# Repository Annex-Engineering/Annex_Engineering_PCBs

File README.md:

# PCBs

PCBs Designed by Annex Engineering Members

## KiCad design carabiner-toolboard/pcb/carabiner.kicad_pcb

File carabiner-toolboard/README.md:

# Carabiner-Toolboard

The carabiner is a toolboard for easy & quick connection between the backpack and toolhead.

It was inspired by the first iterations of dumbboard by LukesLab and designed to bring the idea of a 'simple toolboard' to the next level!

## Features

- Input via 16pin horizontal/vertical microfit
- Two outputs for partcooling fans
- Soldered seperate voltage selection for hotend fan and partcooling fan
   - Uses either the hotend voltage or one alternative voltage
- Thermistor for the chamber
  - Supports any size from 0603 to 1206
- BAT85 diode for inductive probes

## Connectors & Amperage

_Note: All amperage-values have been designed to work in an enclosed printer with up to 65° chamber temperature & have  some safety margins. While you could use higher ampere in an open-frame printer, it's highly discouraged. <br/>
When multiple connectors are supported **bold** marks the recommended connector._

|   | Supported Connectors | Maximum Ampere |
| ------------- | ------------- | ------------- | 
| Hotend  | 2-pin JST XH <br/> Microfit 430450227 <br/> **Microfit 436500227** (compatible with e3d heater) | ~2 Ampere (50W heater on 24V) <br/> 4.2 Ampere (100W heater on 24V) <br/>4.2 Ampere (100W heater on 24V)
| Hotend Thermistor  | 2-pin JST XH <br/> **Microfit 436500227** (compatible with e3d thermistor) | / <br/> /
| Hotend Fan | 2-pin JST XH | 1 Ampere
| 2x Partcooling Fan | 2-pin JST XH | 2 Ampere (total for both)
| Stepper | 4-pin JST XH | 1.2 Ampere <br/> 0.84 Ampere on TMC drivers as you specify the RMS ampere which is ~70% of peak
| Aux / Probe | 4-pin JST XH | 0.8 Ampere

## BOM / Parts

Find the latest BOM in the [Annex Sourcing Guide](https://docs.google.com/spreadsheets/d/1O3eyVuQ6M4F03MJSDs4Z71_XyNjXL5HFTZr1jsaAtRc) under PCBs

## Build Guide

[Please check out this simple written build guide](buildguide/README.md).

## Wiring Guide

This pinout assumes you're looking directly at the cable. 

| PinNumber | Usage  | Silk on PCB | PinNumber | Usage | Silk on PCB | 
|-------------|:-------------:|:-------------:| ------------- |:-------------:|:-------------:|
| 1  |  Thermistor Chamber | ThChamb | 9 | Hotend Voltage | Main+
| 2  | Partcooling Fans Ground | PCF- | 10 | Hotend Ground | HE-
| 3  | Hotend Fan Ground | HEF- | 11 | Alt Voltage | Alt+
| 4  | Thermistor Common Ground | ThGnd | 12 | Thermistor Hotend | ThHE
| 5  | Motor A | 1A | 13 | Motor C | 2A
| 6  | Motor B | 1B | 14 | Motor D | 2B
| 7  | Aux 1 | A1 | 15 | Aux 2 | A2
| 8  | Aux 4 | A4 | 16 | Aux 3 | A3

## Gallery

Side A and B of the R1.1 PCB

## Discord
Our discord server can be found here:

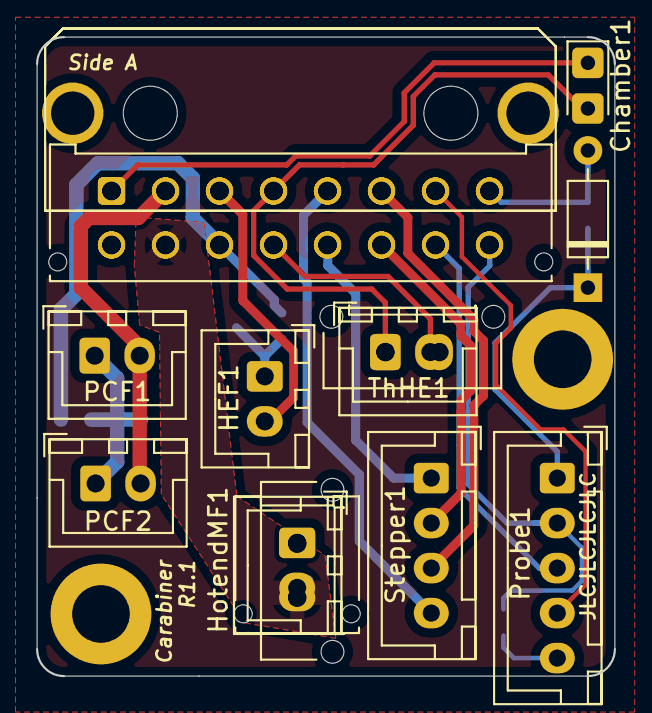
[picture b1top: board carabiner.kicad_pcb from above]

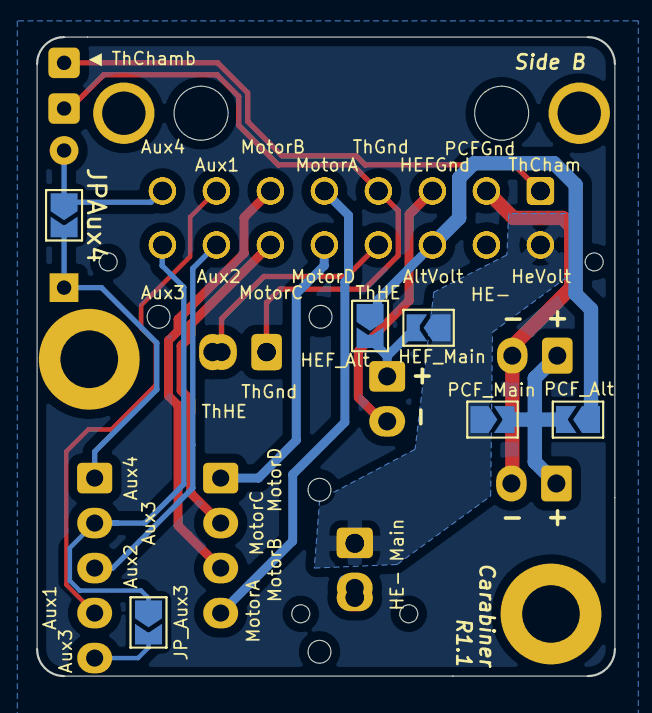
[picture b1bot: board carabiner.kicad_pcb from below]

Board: 2 copper layers, 32.1 x 35.5 mm, 25 parts (6 on the bottom side), 20 nets.

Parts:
Chamber1: Thermistor; 0603_to_1206_THT
D1: B350; D_DO-35_SOD27_P7.62mm_Horizontal
H1, H2: MountingHole; MountingHole_3.2mm_M3_DIN965_Pad
HEF1: HotendFan; JST_XH_B2B-XH-A_1x02_P2.50mm_Vertical
HEF_Alt: SolderJumper_2_Open; SolderJumper-2_P1.3mm_Open_TrianglePad1.0x1.5mm
HEF_Main: SolderJumper_2_Open; SolderJumper-2_P1.3mm_Open_TrianglePad1.0x1.5mm
HotendMF1: Hotend MF 43650-0215; Molex_Micro-Fit_3.0_43650-0215_1x02_P3.00mm_Vertical
HotendMF2: Hotend MF 43045-0212; Molex_Micro-Fit_3.0_43045-0212_2x01_P3.00mm_Vertical
HotendXH1: HotendXHTool; JST_XH_B2B-XH-A_1x02_P2.50mm_Vertical
J1: MF-Vertical 43045-1612; Molex_Micro-Fit_3.0_43045-1612_2x08_P3.00mm_Vertical
J2: MF-Horizontal 43045-1621; Molex_Micro-Fit_3.0_43045-1621_2x08-1MP_P3.00mm_Horizontal
J7: MF-Horizontal 43045-1600; Molex_Micro-Fit_3.0_43045-1600_2x08_P3.00mm_Horizontal
JPAux4: SolderJumper_2_Open; SolderJumper-2_P1.3mm_Open_TrianglePad1.0x1.5mm
JP_Aux3: SolderJumper_2_Open; SolderJumper-2_P1.3mm_Open_TrianglePad1.0x1.5mm
LOGO1: Logo_Open_Hardware_Small; AnnexLogo
LOGO2: Logo_Open_Hardware_Small; AnnexLogoBack
PCF1: PcFan1; JST_XH_B2B-XH-A_1x02_P2.50mm_Vertical
PCF2: PcFan2; JST_XH_B2B-XH-A_1x02_P2.50mm_Vertical
PCF_Alt: SolderJumper_2_Open; SolderJumper-2_P1.3mm_Open_TrianglePad1.0x1.5mm
PCF_Main: SolderJumper_2_Open; SolderJumper-2_P1.3mm_Open_TrianglePad1.0x1.5mm
Probe1: Probe; JST_XH_B5B-XH-A_1x05_P2.50mm_Vertical
Stepper1: E-Stepper; JST_XH_B4B-XH-A_1x04_P2.50mm_Vertical
ThHE1: Thermistor; JST_XH_B2B-XH-A_1x02_P2.50mm_Vertical
ThHe_MF1: Thermistor MF 43650-0215; Molex_Micro-Fit_3.0_43650-0215_1x02_P3.00mm_Vertical

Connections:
A1: J1.7, J2.7, J7.7, Probe1.4
A2: J1.15, J2.15, J7.15, Probe1.3
A3: J1.16, J2.16, J7.16, JP_Aux3.1 (A), Probe1.2
A4: D1.2 (A), J1.8, J2.8, J7.8, JPAux4.1 (A)
AltVolt: HEF_Alt.1 (A), J1.11, J2.11, J7.11, PCF_Alt.1 (A)
Dio_A4: D1.1 (K), JPAux4.2 (B), Probe1.1
HotendFanGnd: HEF1.2, J1.3, J2.3, J7.3
HotendFanSwitch: HEF1.1, HEF_Alt.2 (B), HEF_Main.2 (B)
HotendNeg: HotendMF1.2, HotendMF2.2, HotendXH1.2, J1.10, J2.10, J7.10
HotendVoltage: HEF_Main.1 (A), HotendMF1.1, HotendMF2.1, HotendXH1.1, J1.9, J2.9, J7.9, PCF_Main.1 (A)
unnamed: JP_Aux3.2 (B), Probe1.5
PcFanGnd: J1.2, J2.2, J7.2, PCF1.2, PCF2.2
PcFanSwitch: PCF1.1, PCF2.1, PCF_Alt.2 (B), PCF_Main.2 (B)
Stepper1A: J1.5, J2.5, J7.5, Stepper1.4
Stepper1B: J1.6, J2.6, J7.6, Stepper1.3
Stepper2A: J1.14, J2.14, J7.14, Stepper1.2
Stepper2B: J1.13, J2.13, J7.13, Stepper1.1
ThChamber: Chamber1.1, J1.1, J2.1, J7.1
ThCommonGnd: Chamber1.2, J1.4, J2.4, J7.4, ThHE1.1, ThHe_MF1.1
ThHotend: J1.12, J2.12, J7.12, ThHE1.2, ThHe_MF1.2

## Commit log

2020-08-03 initialize repo
2020-08-03 Beta 0.1 of carabiner toolboard
2020-08-03 Update README.md
    remove internal internal test repo link
2020-08-23 Beta 0.1.1 of carabiner
2020-10-31 move bom to sourcing guide page
2020-10-31 add piton probe to repo - alpha 1
2020-11-01 add mosquito net to repo
2020-11-17 add 6x3 magnet variant
2020-11-18 double stack magnets on the probe side
2020-11-18 print orientation
2020-11-18 add clearance cutout for connector pins
2020-11-19 Alpha 0.2 of Piton PCB
2020-11-19 looser press fit (was breaking part), more magnet exposed
2020-12-20 Carabiner Beta 0.2.1 Modified mounting schema (left mounting hole moved down) Modified layout of the connectors Made the horizontal MF compatible with the vertical MF (before mixing them on the 'rece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
2021-01-08 Carabiner Beta 0.2.2
    [REFACTORING]
    Rename nets to be more clear & consistent.
    Refactor labels to be have more concise names
    Rework traceWidth of the new nets (thinner, still more than enough power)
    [FEATURE]
    Split up 3-pronged jumper voltage jumper into 2 seperate ones.
2021-01-26 Carabiner Beta 0.2.3
    Fix traces being too small (too little amperage supported)
    Update README
2021-06-05 Updated 3d models (included both step and parasolids)to latest 0.2.3 and removed old models. Work done by iKirin!
2021-06-17 Delete Carabiner THT Stencil.stl
    removed out of date stencil, new stencil will be made when time permits.
2021-06-23 Carabiner R1 - 'Unlimited Power'
    Increase maximum hotend amperage (100W heaters are now supported!)
    Minor silkscreen adaptions
    Add folders for attachments & variants
2021-06-24 Add Afterburner support
2021-07-19 Release 1.0.1
    Adapt the footprint for the ChamberResistor to be space apart 2.54mm to support a JST XH connector there
    Rename the outdated nets for the Aux-Port
    Redo the schematic
    Add wiring guide to README.md
    Add build-guide with pictures
2021-08-29 add s6 expander bridge to repo
2021-09-19 Add Carabiner R1 soldering jig
2021-09-23 Add files via upload
    Added iKirin's NEMA-17 bracket
2021-11-25 Add MicroFit support for Afterburner attachment
2021-11-25 Add pictures
2021-12-12 Carabiner R1.1 - 'Who even needs more pins?'
    Duplicates Aux3 - this allows you to wire up a BLTouch much easier
    Increase the maximum ampere for PCFs to 2A total
2022-01-07 Update README.md
    Update FanAmperage to reflect changes in R1.1
2022-02-14 move mosquito net to the misc repo
2022-03-31 Add render
2022-03-31 Add picture of PCB
2022-07-05 move piton to archive
2022-08-21 Carabiner R 1.2 - Polishing it
    - Renaming ports to fit the new unified naming scheme.
    - Updated Readme to reflect that
    - Support USB with the Aux ports! Use A2 and A3 for D+/D-
    - Rework the motor trace routing
2022-08-21 Carabiner Distributor - Alpha 0.1
    First Alpha of the distributor for the backpack.
    This thing should be solid.
2022-09-12 add crampon to repo
2022-09-14 crampon: add instructions and sample config.
2022-09-14 crampon: save readme file in editor before committing.
2022-09-15 Minor updates
2022-09-24 Add renders, readme/ do cleanup / restructure
2022-09-24 Update table
2022-09-24 Update crampon readme
2022-10-23 Carabiner R1.2.1 - Fix all the things
    - Fix disconnected A3 port (the 5th pin that duplicated A3 was disconnected)
    - Match data lines closer - now within 0.04mm in length!
2022-11-14 add cm cad
2022-11-14 add mounting bracket
2022-11-24 add color to sleeving and heatshrink
2023-03-07 crampon_anchor: add a link to new firmware option
2023-03-12 add updated clampon
2023-03-18 Rework K3rabiner information
2023-03-18 Update images distributor
2023-03-18 Add dimensions distributor
2023-03-30 crampon readme: present firmware options better.
2023-04-08 add icescrew black pill edition
2023-04-08 add images
2023-04-08 add sourcing link
2023-04-23 Add Legacy Bracket back
2023-06-14 add flashing instructions
2023-11-21 housekeeping, as k3rabiner is on k3 repo
2024-07-17 remove carabiner from distro
